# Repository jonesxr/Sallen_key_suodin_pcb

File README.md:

# Aktiivinen Sallen-Key Alipäästösuodin

Projektissa toteutettiin 2. asteen aktiivisen Sallen-Key alipäästösuodin. Projekti sisältää sähkökaavion, piirilevyn layoutin sekä toimivan SPICE-simuloinnin ngspicellä.

## Sähkökaavio

_Suotimen sydän on TL072 dual JFET -operaatiovahvistin. Vastukset R1 ja R2 (11 kΩ) sekä kondensaattorit C1 (10 nF) ja C2 (22 nF) muodostavat varsinaisen suodatinpiirin. Käyttöjännite on ±12 V, ja ohituskondensaattorit C3 ja C4 (100 nF) pitävät käyttöjännitteen vakaana. Alakulmassa olevat jännitelähteet ovat simulaatiota varten._

## PCB-layout

_Piirilevy on suunniteltu kaksipuolisena. Komponentit on sijoiteltu etupuolelle ja takapuolella on yhtenäinen maataso (GND), joka auttaa häiriöiden torjunnassa._

## 3D-näkymä

_Tältä valmis levy näyttäisi. Kaikki komponentit ovat läpiladottavia (THT), eli levy on helppo juottaa käsin._

## Simulointitulokset

_AC-analyysin tulos ngspicestä. Punainen käyrä on tulosignaali ja sininen lähtösignaali. Rajataajuudella (~1 kHz) vaimennus on -3 dB, ja sen jälkeen signaali vaimenee jyrkästi -40 dB/dekadi. Katkoviivat näyttävät vaihevasteen._

## DRC-tarkistus

_Design Rule Check läpi ilman virheitä tai varoituksia._

## Komponentit

| Komponentti | Arvo                     | Kotelo     |
| ----------- | ------------------------ | ---------- |
| U1          | TL072 (Dual JFET Op-Amp) | DIP-8      |
| R1, R2      | 11 kΩ                    | Axiaalinen |
| C1          | 10 nF                    | Levy       |
| C2          | 22 nF                    | Levy       |
| C3, C4      | 100 nF (ohitus)          | Levy       |

## Rajataajuus

```
f_c = 1 / (2π × √(R1×R2×C1×C2))
f_c = 1 / (2π × √(11k × 11k × 10n × 22n))
f_c ≈ 1.03 kHz
```

## Simuloinnin vianmääritys

Simuloinnin kanssa tuli vastaan useampi ongelma ennen kuin homma alkoi pelittää. Tässä dokumentoituna mitä meni pieleen ja miten asiat korjattiin.

### 1. TL072:n SPICE-malli ei toiminut ngspicellä

ngspice antoi virheen:

```
Undefined parameter [i]
Expression err: 4.715e6*i(vb)-5e6*i(vc)+5e6*i(ve)+5e6*i(vlp)-5e6*i(vln)}
```

TI:n alkuperäinen malli käyttää `POLY`-syntaksia, jota ngspice ei ymmärrä. Ensin yritin `VALUE { }` -syntaksia, mutta sekään ei toiminut F-elementeillä (ngspice 44 ei tue sitä). Lopulta ratkaisu oli vaihtaa B-elementteihin:

```diff
- EGND 99  0 VALUE { 0.5*V(3) + 0.5*V(4) }
- FB    7 99 VALUE { 4.715E6*I(VB) - 5E6*I(VC) + 5E6*I(VE) + 5E6*I(VLP) - 5E6*I(VLN) }
+ BEGND 99  0 V = 0.5*V(3) + 0.5*V(4)
+ BFB   7 99 I = 4.715E6*I(VB) - 5E6*I(VC) + 5E6*I(VE) + 5E6*I(VLP) - 5E6*I(VLN)
```

### 2. Pinnit olivat väärin päin

Simulointi pyörähti käyntiin, mutta tulos näytti ylipäästösuotimelta – ei todellakaan se mitä haettiin. Syy oli yksinkertainen: TL072:n fyysiset DIP-8 pinnit oli mapattu väärin SPICE-mallin pinneihin.

```
TL072 DIP-8:
        ┌──U──┐
  OUT_A │1   8│ V+
   IN-_A│2   7│ OUT_B
   IN+_A│3   6│ IN-_B
     V- │4   5│ IN+_B
        └─────┘
```

SPICE-mallin pinnijärjestys on `1=Non-inv, 2=Inv, 3=V+, 4=V-, 5=Out`, joten oikea mappaus on:

```
Unit 1 (Op-Amp A): Sim.Pins = "3=1 2=2 8=3 4=4 1=5"
Unit 2 (Op-Amp B): Sim.Pins = "5=1 6=2 8=3 4=4 7=5"
```

### 3. Sim-kentissä oli tuplat

```
Error: Not enough tokens in line 16
u1 __u1
```

U1-symbolille oli jotenkin päätynyt kaksi sarjaa `Sim.*`-kenttiä – toisessa sarjassa kenttien nimissä oli ylimääräinen välilyönti perässä (esim. `"Sim.Device "` vs `"Sim.Device"`). Duplikaattien poisto korjasi ongelman.

### 4. Liittimet sotkivat simuloinnin

```
Error: Not enough tokens in line 21
output1 __output1
```

Input1- ja Output1-liittimet päätyivät SPICE-netlistiin vaikka niillä ei ole SPICE-mallia. Ratkaisu: `exclude_from_sim = yes` liittimille, ja tuloon oma VSIN-jännitelähde.

## Mitä tästä oppi

- **POLY ei toimi ngspicellä** – käytä B-elementtejä (`V =` ja `I =` syntaksi) sen sijaan
- **Dual op-ampin pinnimappaus** on tehtävä erikseen jokaiselle yksikölle vastaamaan fyysistä DIP-8 pinoutia
- **Fyysiset liittimet** pitää jättää simuloinnin ulkopuolelle (`exclude_from_sim = yes`)

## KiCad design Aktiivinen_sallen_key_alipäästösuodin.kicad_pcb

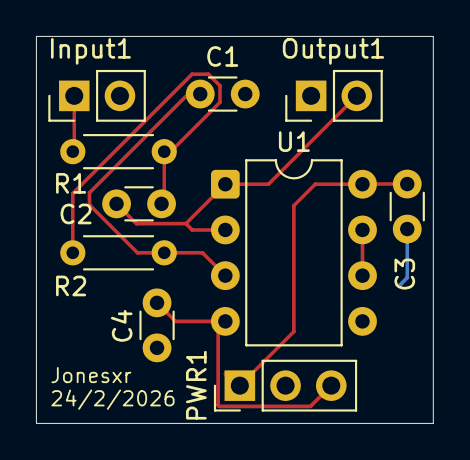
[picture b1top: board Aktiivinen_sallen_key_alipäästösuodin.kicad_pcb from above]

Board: 2 copper layers, 22.1 x 21.5 mm, 10 parts (0 on the bottom side), 8 nets.

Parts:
C1: 10nF; C_Disc_D3.0mm_W1.6mm_P2.50mm
C2: 22nF; C_Disc_D3.0mm_W1.6mm_P2.50mm
C3, C4: 100nF; C_Disc_D3.0mm_W1.6mm_P2.50mm
Input1: dc=0 ampl=1 f=100 td=0 theta=0 phase=0 ac=1; PinHeader_1x02_P2.54mm_Vertical
Output1: Conn_01x02_Pin; PinHeader_1x02_P2.54mm_Vertical
PWR1: Conn_01x03_Pin; PinHeader_1x03_P2.54mm_Vertical
R1, R2: 11k; R_Axial_DIN0204_L3.6mm_D1.6mm_P5.08mm_Horizontal
U1: TL072; DIP-8_W7.62mm

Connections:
+12V: C3.2, PWR1.1, U1.8 (V+)
-12V: C4.2, PWR1.3, U1.4 (V-)
GND: C1.2, C3.1, C4.1, Input1.2, Output1.1, PWR1.2, U1.5 (+)
unnamed: C2.1, R1.2, R2.1
unnamed: Input1.1, R1.1
unnamed: C2.2, Output1.2, U1.1, U1.2 (-)
unnamed: C1.1, R2.2, U1.3 (+)
unnamed: U1.6 (-), U1.7

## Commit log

2026-02-24 korjauksia
2026-02-24 kuva muutettu
2026-02-24 Korjaa kirjoitusvirhe README.md:ssä
2026-02-24 Revert "Korjaa kirjoitusvirhe README.md:ssä"
    This reverts commit 802c27a3e14bd099216c014f139f2ede624727c5.
2026-02-24 korjattu kirjoitusvirh
